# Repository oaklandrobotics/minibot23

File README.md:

# MiniBot 2023

Welcome to the MiniBot 2023 project! This repository serves as the documentation and codebase for our 2023 MiniBot project.

## Table of Contents

- [Introduction](#introduction)
- [Getting Started](#getting-started)
- [Documentation](#documentation)
- [Contributing](#contributing)

## Introduction

The MiniBot 2023 project is designed to provide club members with hands-on experience and training opportunities. This README will provide background information as well as instructions on how to get started. 

## Getting Started

To get started with the MiniBot 2023 project, follow these steps:

1. Clone this repository to your local machine:

   ```bash
   git clone https://github.com/oaklandrobotics/MiniBot-2023.git

## Documentation

W.I.P

## Contributing

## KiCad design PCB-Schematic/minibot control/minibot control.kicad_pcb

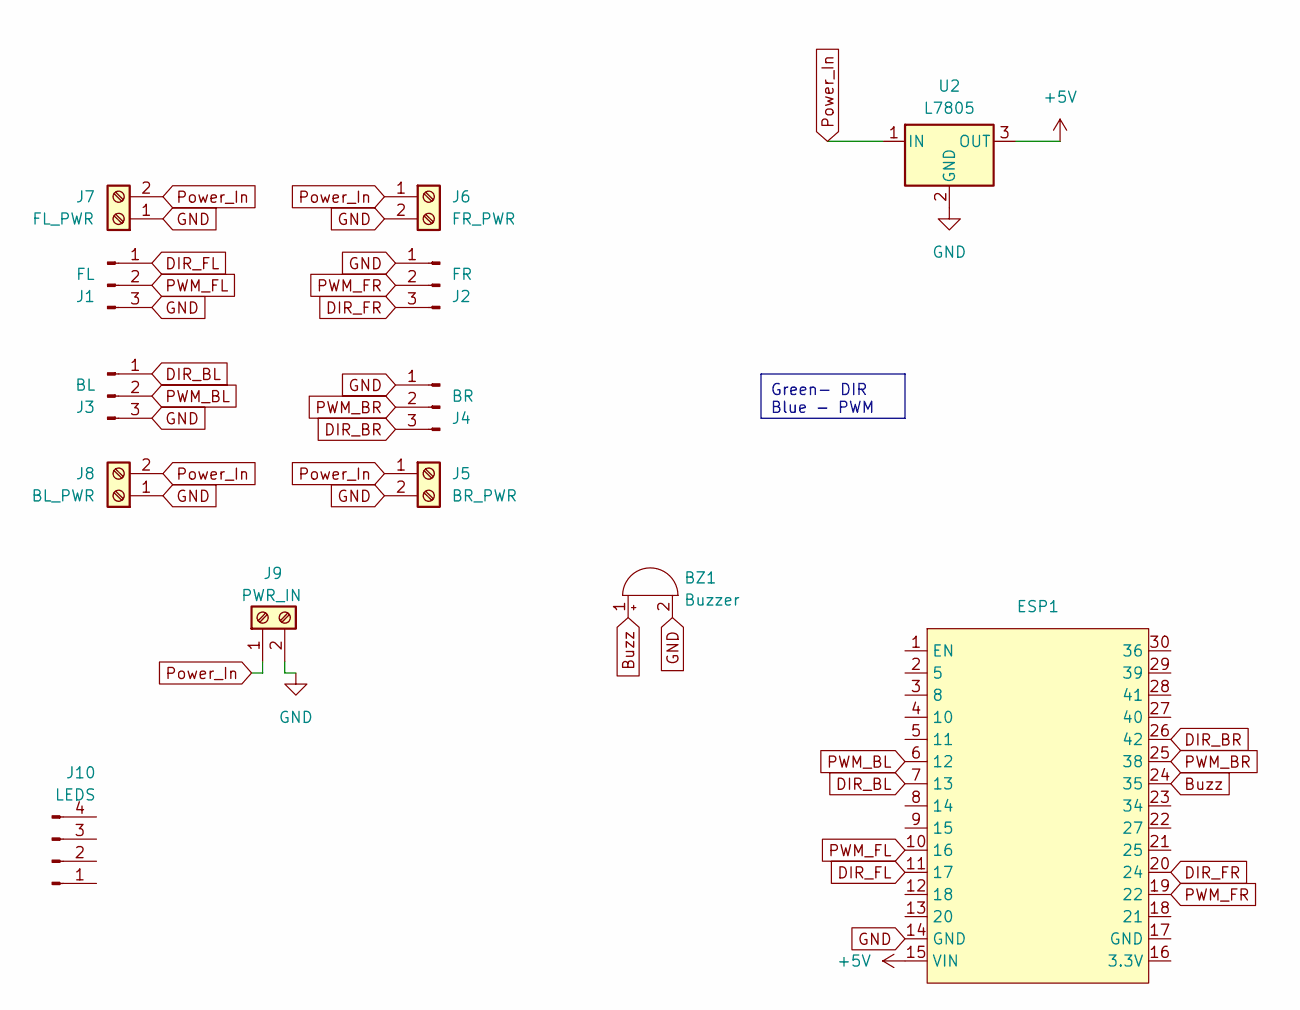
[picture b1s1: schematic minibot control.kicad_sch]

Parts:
BZ1: Buzzer; Buzzer_12x9.5RM7.6
ESP1: ESP-32
J1: FL; PinHeader_1x03_P2.54mm_Vertical
J2: FR; PinHeader_1x03_P2.54mm_Vertical
J3: BL; PinHeader_1x03_P2.54mm_Vertical
J4: BR; PinHeader_1x03_P2.54mm_Vertical
J5: BR_PWR; TerminalBlock_TE_282834-2_1x02_P2.54mm_Horizontal
J6: FR_PWR; TerminalBlock_TE_282834-2_1x02_P2.54mm_Horizontal
J7: FL_PWR; TerminalBlock_TE_282834-2_1x02_P2.54mm_Horizontal
J8: BL_PWR; TerminalBlock_TE_282834-2_1x02_P2.54mm_Horizontal
J9: PWR_IN; TerminalBlock_TE_282834-2_1x02_P2.54mm_Horizontal
J10: LEDS; PinHeader_1x04_P2.54mm_Vertical
U2: L7805; TO-3P-3_Vertical

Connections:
+5V: ESP1.15 (VIN), U2.3 (OUT)
Buzz: BZ1.1 (-), ESP1.24 (35)
DIR_BL: ESP1.7 (13), J3.1
DIR_BR: ESP1.26 (42), J4.3
DIR_FL: ESP1.11 (17), J1.1
DIR_FR: ESP1.20 (24), J2.3
GND: BZ1.2 (+), ESP1.14 (GND), J1.3, J2.1, J3.3, J4.1, J5.2, J6.2, J7.1, J8.1, J9.2, U2.2 (GND)
PWM_BL: ESP1.6 (12), J3.2
PWM_BR: ESP1.25 (38), J4.2
PWM_FL: ESP1.10 (16), J1.2
PWM_FR: ESP1.19 (22), J2.2
Power_In: J5.1, J6.1, J7.2, J8.2, J9.1, U2.1 (IN)

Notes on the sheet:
Green- DIR Blue - PWM

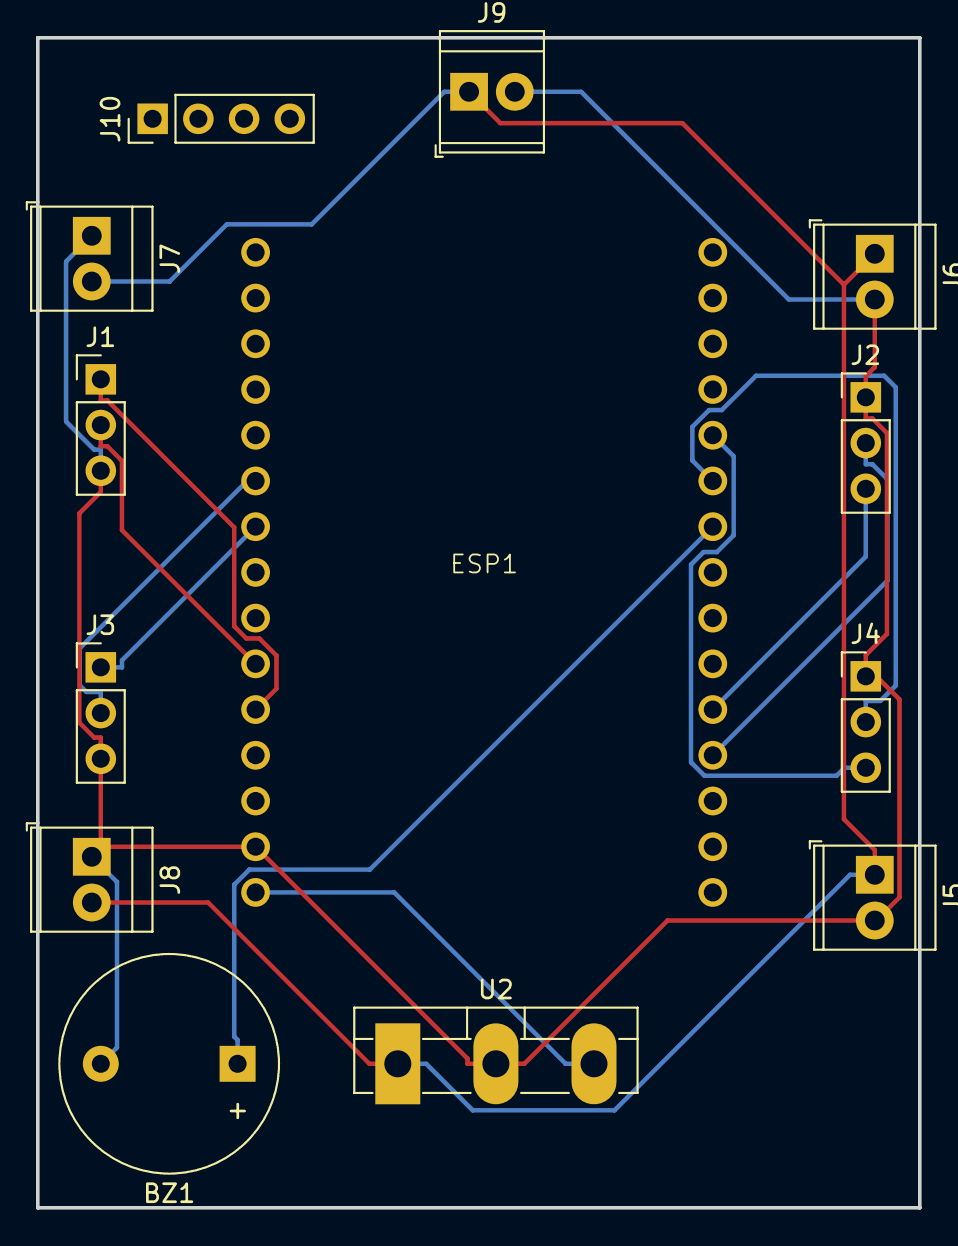
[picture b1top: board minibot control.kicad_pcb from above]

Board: 2 copper layers, 49.0 x 65.0 mm, 13 parts (0 on the bottom side), 12 nets.

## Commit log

2023-09-23 Initial Code Dump
2023-10-14 Update pinouts for current layout
2024-02-01 I forgor to upload
2024-09-27 Fix the pins, add delay
    Thanks to George for his energy.
2024-10-25 Fix back motor pins, add PS4 support
2024-10-26 Fix deadband again and speed clamping
